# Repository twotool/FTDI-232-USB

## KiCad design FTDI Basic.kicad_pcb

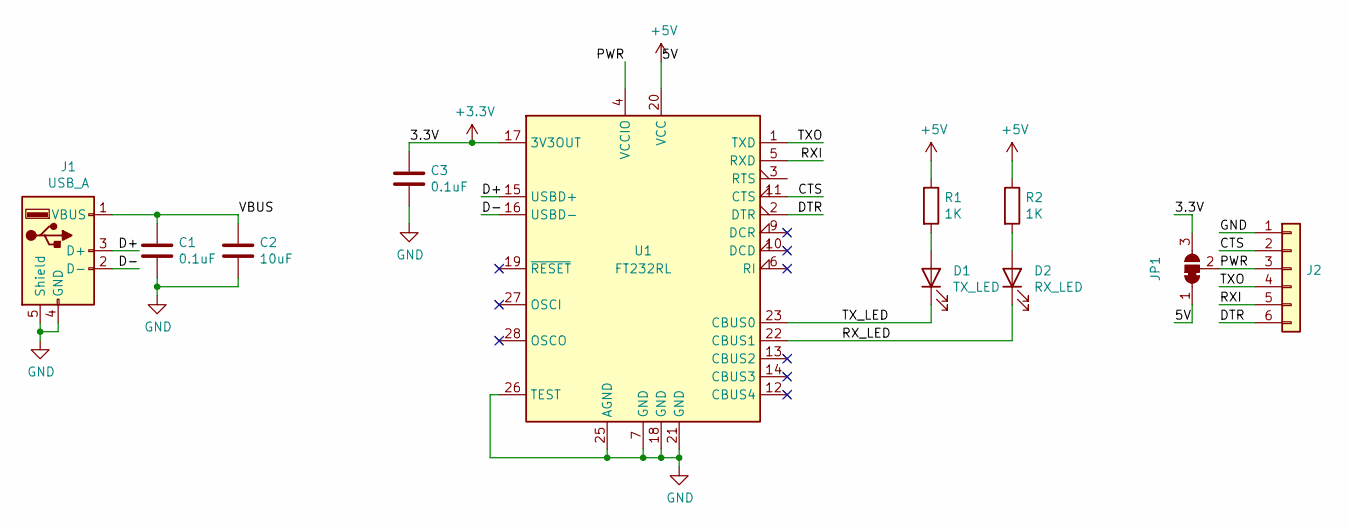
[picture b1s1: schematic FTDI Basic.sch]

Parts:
C1, C3: 0.1uF; C_0603_1608Metric
C2: 10uF; C_0603_1608Metric
D1: TX_LED; LED_0603_1608Metric
D2: RX_LED; LED_0603_1608Metric
J1: USB_A; USB_A_CNCTech_1001-011-01101_Horizontal
J2: Conn_01x06; PinHeader_1x06_P2.54mm_Horizontal
JP1: SolderJumper_3_Bridged12; SolderJumper-3_P1.3mm_Bridged2Bar12_Pad1.0x1.5mm
R1, R2: 1K; R_0603_1608Metric
U1: FT232RL; SSOP-28_5.3x10.2mm_P0.65mm

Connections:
+3V3: C3.1, JP1.3 (B), U1.17 (3V3OUT)
+5V: JP1.1 (A), R1.1, R2.1, U1.20 (VCC)
/CTS: J2.2, U1.11 (CTS)
/D+: J1.3 (D+), U1.15 (USBD+)
/D-: J1.2 (D-), U1.16 (USBD-)
/DTR: J2.6, U1.2 (DTR)
/PWR: J2.3, JP1.2 (C), U1.4 (VCCIO)
/RXI: J2.5, U1.5 (RXD)
/RX_LED: D2.1 (K), U1.22 (CBUS1)
/TXO: J2.4, U1.1 (TXD)
/TX_LED: D1.1 (K), U1.23 (CBUS0)
/VBUS: C1.1, C2.1, J1.1 (VBUS)
GND: C1.2, C2.2, C3.2, J1.4 (GND), J1.5 (Shield), J2.1, U1.7 (GND), U1.18 (GND), U1.21 (GND), U1.25 (AGND), U1.26 (TEST)
unnamed: D1.2 (A), R1.2
unnamed: D2.2 (A), R2.2

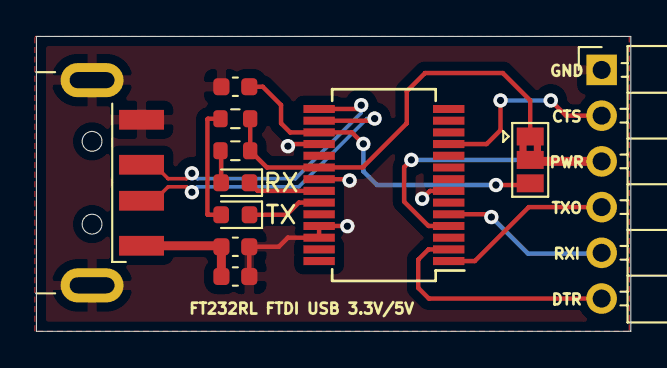
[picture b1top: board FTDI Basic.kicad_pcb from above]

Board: 2 copper layers, 33.0 x 16.4 mm, 11 parts (0 on the bottom side), 15 nets.
